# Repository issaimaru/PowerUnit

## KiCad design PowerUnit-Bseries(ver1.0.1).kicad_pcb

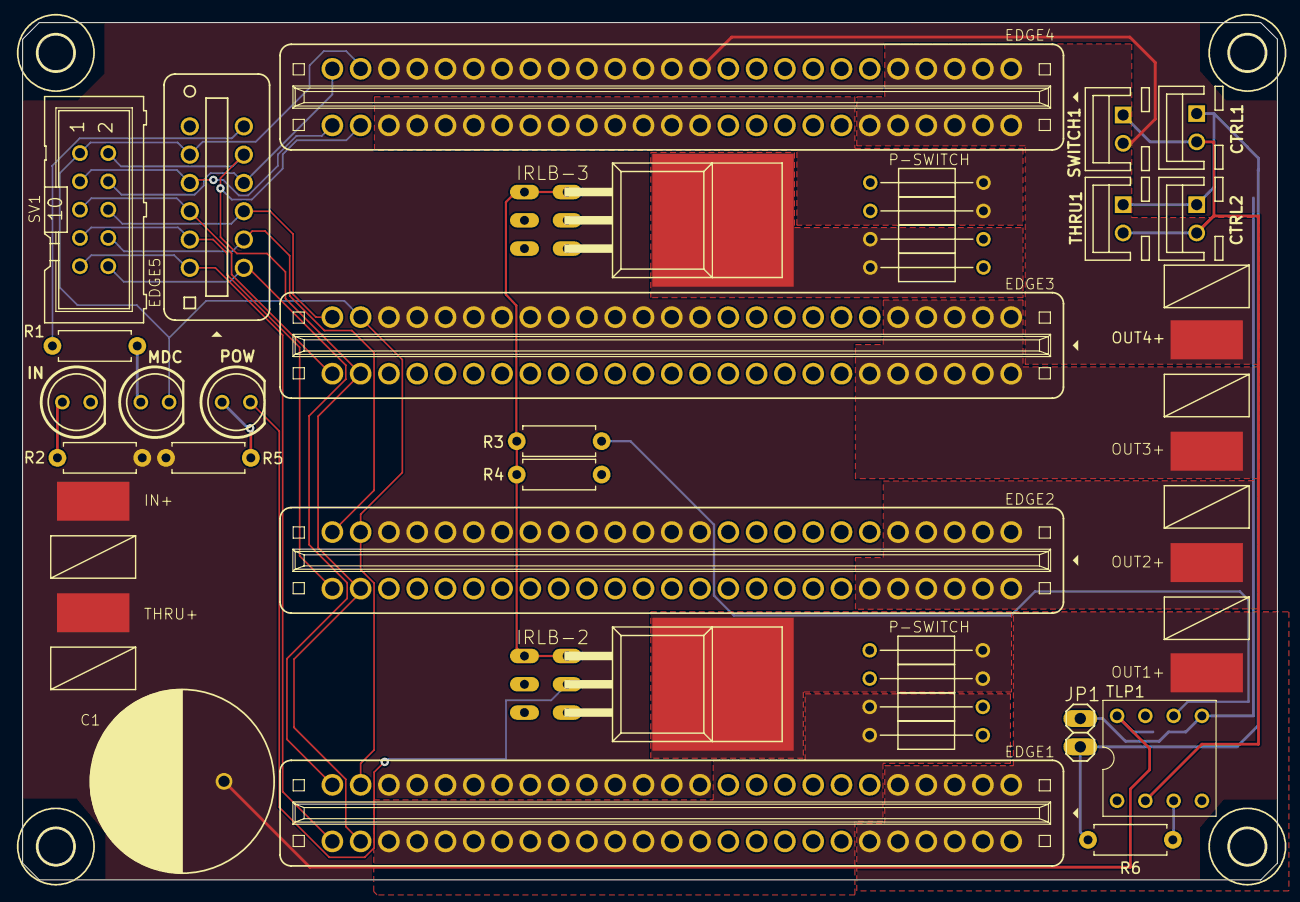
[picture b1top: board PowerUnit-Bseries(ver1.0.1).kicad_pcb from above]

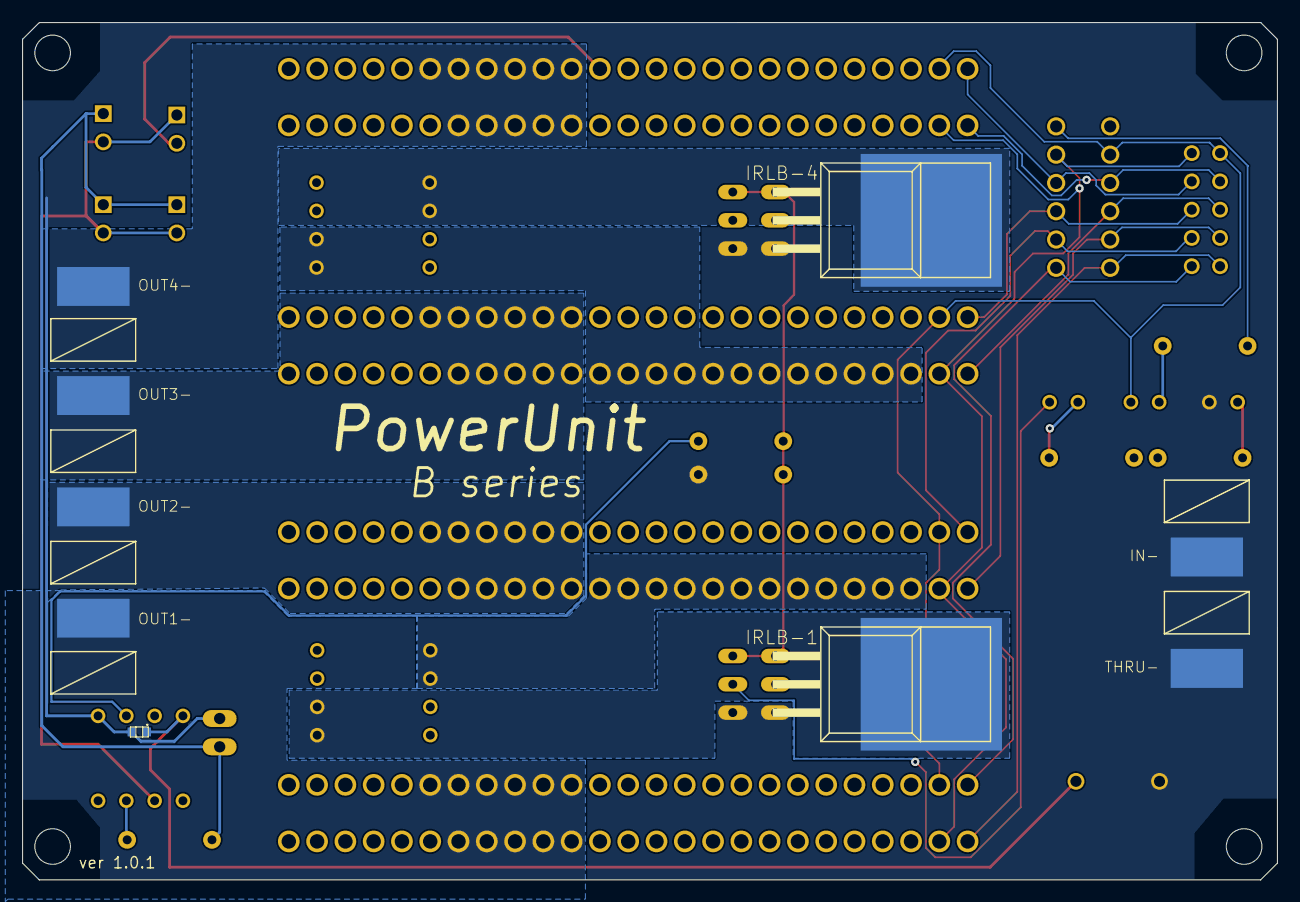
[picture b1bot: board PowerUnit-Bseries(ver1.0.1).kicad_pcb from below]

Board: 2 copper layers, 112.7 x 77.0 mm, 51 parts (9 on the bottom side), 38 nets.

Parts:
C1: 50ZLH1000MEFC16X25
C2: GCM188L81H104KA57
CTRL1, CTRL2: 02-JST; B2B-XH
EDGE1, EDGE2, EDGE3, EDGE4: 10046971-019LF-FEMAL; 10046971-019LF
EDGE5: 7-5530843-6
H1, H2, H3, H4: MOUNT-HOLE3.2; 3,2
IN+: PADS14; AWG14
IN-: PADS14; AWG14
IRLB-1, IRLB-2, IRLB-3, IRLB-4: IRLB3813_2; TO-220AB-PUT
JP1: PINHD-1X2; 1X02
LED1, LED2, LED3: LED5MM
OUT1+, OUT1-, OUT2+, OUT2-, OUT3+, OUT3-, OUT4+, OUT4-: PADS14; AWG14
P-1, P-2, P-3, P-4, P-5, P-6, P-7, P-8: P-SWITCH
R1: 100; R_Axial_DIN0207_L6.3mm_D2.5mm_P7.62mm_Horizontal
R2, R5: 680; R_Axial_DIN0207_L6.3mm_D2.5mm_P7.62mm_Horizontal
R3, R6: 1k; R_Axial_DIN0207_L6.3mm_D2.5mm_P7.62mm_Horizontal
R4: 10k; R_Axial_DIN0207_L6.3mm_D2.5mm_P7.62mm_Horizontal
SV1: ML10
SWITCH1: 02-JST; B2B-XH
THRU1: 02-JST; B2B-XH
THRU+: PADS14; AWG14
THRU-: PADS14; AWG14
TLP1: 2227MC-08-03

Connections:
/DIR1: EDGE1.P$26 (P26), EDGE5.P$12 (P12), SV1.9
/DIR2: EDGE2.P$26 (P26), EDGE5.P$11 (P11), SV1.7
/DIR3: EDGE3.P$26 (P26), EDGE5.P$10 (P10), SV1.5
/DIR4: EDGE4.P$26 (P26), EDGE5.P$9 (P9), SV1.3
/GND2: EDGE1.P$24 (P24), EDGE2.P$24 (P24), EDGE3.P$24 (P24), EDGE4.P$24 (P24), EDGE5.P$8 (P8), LED2.K (C), SV1.1
/LED: EDGE5.P$6 (P6), R1.1
/PWM1: EDGE1.P$25 (P25), EDGE5.P$1 (P1), SV1.10
/PWM2: EDGE2.P$25 (P25), EDGE5.P$2 (P2), SV1.8
/PWM3: EDGE3.P$25 (P25), EDGE5.P$3 (P3), SV1.6
/PWM4: EDGE4.P$25 (P25), EDGE5.P$4 (P4), SV1.4
/VCC2: EDGE1.P$27 (P27), EDGE2.P$27 (P27), EDGE3.P$27 (P27), EDGE4.P$27 (P27), EDGE5.P$5 (P5), SV1.2
GND: C1.C (CATHODE), C2.P$2, IN-.P$1, IRLB-1.S, IRLB-2.S, IRLB-3.S, IRLB-4.S, JP1.1, LED1.K (C), R4.2, THRU-.P$1, TLP1.P$5 (GND)
unnamed: CTRL1.1, CTRL2.1, JP1.2, R6.1, THRU1.1
unnamed: EDGE1.P$1 (P1), EDGE1.P$2 (P2), EDGE1.P$3 (P3), EDGE1.P$4 (P4), EDGE1.P$5 (P5), EDGE1.P$45 (P45), EDGE1.P$46 (P46), EDGE1.P$47 (P47), EDGE1.P$48 (P48), EDGE1.P$49 (P49), EDGE1.P$50 (P50), OUT1+.P$1
unnamed: EDGE1.P$6 (P6), EDGE1.P$7 (P7), EDGE1.P$8 (P8), EDGE1.P$9 (P9), EDGE1.P$10 (P10), EDGE1.P$11 (P11), EDGE1.P$40 (P40), EDGE1.P$41 (P41), EDGE1.P$42 (P42), EDGE1.P$43 (P43), EDGE1.P$44 (P44), OUT1-.P$1
unnamed: EDGE1.P$28 (P28), EDGE1.P$29 (P29), EDGE1.P$30 (P30), EDGE1.P$31 (P31), EDGE1.P$32 (P32), EDGE1.P$33 (P33), EDGE1.P$34 (P34), EDGE1.P$35 (P35), EDGE1.P$36 (P36), EDGE1.P$37 (P37), EDGE1.P$38 (P38), EDGE1.P$39 (P39), P-1.P$1, P-2.P$1
unnamed: EDGE2.P$1 (P1), EDGE2.P$2 (P2), EDGE2.P$3 (P3), EDGE2.P$4 (P4), EDGE2.P$5 (P5), EDGE2.P$45 (P45), EDGE2.P$46 (P46), EDGE2.P$47 (P47), EDGE2.P$48 (P48), EDGE2.P$49 (P49), EDGE2.P$50 (P50), OUT2+.P$1
unnamed: EDGE2.P$6 (P6), EDGE2.P$7 (P7), EDGE2.P$8 (P8), EDGE2.P$9 (P9), EDGE2.P$10 (P10), EDGE2.P$11 (P11), EDGE2.P$40 (P40), EDGE2.P$41 (P41), EDGE2.P$42 (P42), EDGE2.P$43 (P43), EDGE2.P$44 (P44), OUT2-.P$1
unnamed: EDGE2.P$28 (P28), EDGE2.P$29 (P29), EDGE2.P$30 (P30), EDGE2.P$31 (P31), EDGE2.P$32 (P32), EDGE2.P$33 (P33), EDGE2.P$34 (P34), EDGE2.P$35 (P35), EDGE2.P$36 (P36), EDGE2.P$37 (P37), EDGE2.P$38 (P38), EDGE2.P$39 (P39), P-3.P$1, P-4.P$1
unnamed: EDGE3.P$1 (P1), EDGE3.P$2 (P2), EDGE3.P$3 (P3), EDGE3.P$4 (P4), EDGE3.P$5 (P5), EDGE3.P$45 (P45), EDGE3.P$46 (P46), EDGE3.P$47 (P47), EDGE3.P$48 (P48), EDGE3.P$49 (P49), EDGE3.P$50 (P50), OUT3+.P$1
unnamed: EDGE3.P$6 (P6), EDGE3.P$7 (P7), EDGE3.P$8 (P8), EDGE3.P$9 (P9), EDGE3.P$10 (P10), EDGE3.P$11 (P11), EDGE3.P$40 (P40), EDGE3.P$41 (P41), EDGE3.P$42 (P42), EDGE3.P$43 (P43), EDGE3.P$44 (P44), OUT3-.P$1
unnamed: EDGE3.P$28 (P28), EDGE3.P$29 (P29), EDGE3.P$30 (P30), EDGE3.P$31 (P31), EDGE3.P$32 (P32), EDGE3.P$33 (P33), EDGE3.P$34 (P34), EDGE3.P$35 (P35), EDGE3.P$36 (P36), EDGE3.P$37 (P37), EDGE3.P$38 (P38), EDGE3.P$39 (P39), P-5.P$1, P-6.P$1
unnamed: EDGE4.P$1 (P1), EDGE4.P$2 (P2), EDGE4.P$3 (P3), EDGE4.P$4 (P4), EDGE4.P$5 (P5), EDGE4.P$45 (P45), EDGE4.P$46 (P46), EDGE4.P$47 (P47), EDGE4.P$48 (P48), EDGE4.P$49 (P49), EDGE4.P$50 (P50), OUT4+.P$1
unnamed: EDGE4.P$6 (P6), EDGE4.P$7 (P7), EDGE4.P$8 (P8), EDGE4.P$9 (P9), EDGE4.P$10 (P10), EDGE4.P$11 (P11), EDGE4.P$40 (P40), EDGE4.P$41 (P41), EDGE4.P$42 (P42), EDGE4.P$43 (P43), EDGE4.P$44 (P44), OUT4-.P$1
unnamed: EDGE4.P$28 (P28), EDGE4.P$29 (P29), EDGE4.P$30 (P30), EDGE4.P$31 (P31), EDGE4.P$32 (P32), EDGE4.P$33 (P33), EDGE4.P$34 (P34), EDGE4.P$35 (P35), EDGE4.P$36 (P36), EDGE4.P$37 (P37), EDGE4.P$38 (P38), EDGE4.P$39 (P39), P-7.P$1, P-8.P$1
unnamed: IRLB-1.P$1 (PD), P-1.P$2, P-2.P$2
unnamed: IRLB-1.G, IRLB-2.G, IRLB-3.G, IRLB-4.G, R3.2, R4.1
unnamed: IRLB-2.P$1 (PD), P-3.P$2, P-4.P$2
unnamed: IRLB-3.P$1 (PD), P-5.P$2, P-6.P$2
unnamed: IRLB-4.P$1 (PD), P-7.P$2, P-8.P$2
unnamed: LED1.A, R2.2
unnamed: LED2.A, R1.2
unnamed: IRLB-2.D, LED3.K (C)
unnamed: LED3.A, R5.2
unnamed: CTRL1.2, CTRL2.2, SWITCH1.1, THRU1.2, TLP1.P$2 (ANODE)
unnamed: R6.2, TLP1.P$3 (CATHODE)
unnamed: R3.1, TLP1.P$6 (VOUT)
VCC: C1.A (ANODE), C2.P$1, EDGE1.P$12 (P12), EDGE1.P$13 (P13), EDGE1.P$14 (P14), EDGE1.P$15 (P15), EDGE1.P$16 (P16), EDGE1.P$17 (P17), EDGE1.P$18 (P18), EDGE1.P$19 (P19), EDGE1.P$20 (P20), EDGE1.P$21 (P21), EDGE1.P$22 (P22), EDGE1.P$23 (P23), EDGE2.P$12 (P12), EDGE2.P$13 (P13), EDGE2.P$14 (P14), EDGE2.P$15 (P15), EDGE2.P$16 (P16), EDGE2.P$17 (P17), EDGE2.P$18 (P18), EDGE2.P$19 (P19), EDGE2.P$20 (P20), EDGE2.P$21 (P21), EDGE2.P$22 (P22), EDGE2.P$23 (P23), EDGE3.P$12 (P12), EDGE3.P$13 (P13), EDGE3.P$14 (P14), EDGE3.P$15 (P15), EDGE3.P$16 (P16), EDGE3.P$17 (P17), EDGE3.P$18 (P18), EDGE3.P$19 (P19), EDGE3.P$20 (P20), EDGE3.P$21 (P21), EDGE3.P$22 (P22), EDGE3.P$23 (P23), EDGE4.P$12 (P12), EDGE4.P$13 (P13), EDGE4.P$14 (P14), EDGE4.P$15 (P15), EDGE4.P$16 (P16), EDGE4.P$17 (P17), EDGE4.P$18 (P18), EDGE4.P$19 (P19), EDGE4.P$20 (P20), EDGE4.P$21 (P21), EDGE4.P$22 (P22), EDGE4.P$23 (P23), IN+.P$1, R2.1, R5.1, SWITCH1.2, THRU+.P$1, TLP1.P$8 (VCC)

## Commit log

2025-07-10 add: LICENCEなどの追加
